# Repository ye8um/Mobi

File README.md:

# Mobi — Phone Controlled Two-Wheel Robot

Mobi is a compact, custom-designed Wi-Fi robot with an animated 0.96-inch OLED face. I designed its PCB in KiCad and its rounded enclosure, motor mounts, display opening, and power-bank compartment in Fusion 360. The robot uses a Seeed XIAO ESP32-C3, a TB6612FNG dual motor driver, and two small N20 gear motors. A small ball caster supports the body behind its drive wheels.

The goal is a simple, friendly robot that I can steer from my phone without installing an app. Mobi creates a Wi-Fi network and serves a web controller with directional buttons and a speed slider. The motor control stops when the button is released or commands stop arriving. Its OLED face blinks and shifts its eyes while turning.

## Features

- Phone control over a local Wi-Fi access point, no internet needed
- Forward, reverse, left, right, and stop
- Adjustable speed using PWM motor control
- Animated 128 × 64 OLED eyes
- 450 ms command timeout for a basic motor fail-safe
- Custom two-layer PCB and 3D-printed enclosure
- Two small N20 geared motors and a passive rear ball caster

There is **no obstacle or edge sensor** in this version, so operate it only on a level, clear floor, away from stairs, edges, and fragile objects. This is a hobby robot, not an autonomous robot.

## Hardware overview

Main controller: Seeed XIAO ESP32-C3 with its external Wi-Fi antenna. Motor controller: **bare** TB6612FNG SSOP-24 soldered to the custom PCB; not the breakout module. The TB6612's PWMA, PWMB, and STBY inputs are tied to 3.3 V in this board design. Display: common SSD1306 0.96-inch 128 × 64 **4-wire I2C** module, address usually 0x3C. Power: a commercial 5 V USB power bank, a **proper USB-C 5 V sink breakout**, an adequately rated power switch, and a Schottky diode feeding the XIAO VBUS input.

### Firmware pin map — updated after the pin swap

| XIAO label | GPIO | Function |
|---|---:|---|
| D1 | 3 | TB6612 AIN1 |
| D2 | 4 | TB6612 AIN2 |
| D3 | 5 | TB6612 BIN1 |
| D4 | 6 | TB6612 BIN2 (swapped) |
| D6 | 21 | OLED SDA (swapped) |
| D5 | 7 | OLED SCL |
| 3V3 | — | TB6612 VCC/PWMA/PWMB/STBY and compatible OLED VCC |
| GND | — | Common logic and motor ground |

Connect TB6612 AO1/AO2 to left motor and BO1/BO2 to right motor. Tie all TB6612 motor-supply VM and PGND pads correctly. The motor supply comes from the switched **5 V power input**, not from the XIAO 3.3 V output. The driver requires local decoupling as documented in its datasheet.

The XIAO's 5 V/VBUS supply must follow Seeed's external supply diode guidance. Do not connect the powered robot to your computer's USB port at the same time as its external 5 V source without reviewing the power arrangement.

## Arduino setup

1. Install Arduino IDE and Espressif's `esp32` board package.
2. Choose the **Seeed XIAO ESP32C3** board and its USB port.
3. From Arduino Library Manager install **Adafruit GFX Library** and **Adafruit SSD1306** (with their dependencies).
4. Open `Arduino/Mobi.ino`.
5. Check the pin assignments against the **latest actual KiCad schematic**, especially the changed D4/D6 pins.
6. Change `AP_PASSWORD` in the sketch. Upload the sketch with the robot's external power disconnected.
7. Test with the robot raised so the drive wheels cannot touch the floor. Start at low speed and verify both motor directions and the OLED.
8. Power the assembled robot, connect your phone to `Mobi-Robot`, then open `http://192.168.4.1`.
9. Press and hold a direction button to drive. Release to stop. The STOP button works immediately; a 450 ms timeout covers dropped commands.

If one motor turns backward, set `REVERSE_LEFT` or `REVERSE_RIGHT` to `true` in the sketch, then upload again. If the OLED remains blank, confirm its 3.3 V compatibility, 0x3C I2C address, SDA/SCL wires, and that it really uses an SSD1306 controller.

## CAD and assembly

The current concept has a 120 × 95 mm rounded chassis, a roughly 65 × 50 mm PCB, 2 mm outer walls, and a removable top cover. The display window is in the front. The battery-holder placeholder is 75 × 40 × 15 mm, **not a confirmed power-bank model**. Do not treat that placeholder as a purchase specification.

The motor CAD references are GA12-N20-sized, but must be compared against the purchased motor shaft and bracket dimensions. Wheel diameter changes the axle height, and the caster must touch the same floor plane as both wheels. For a 32 mm wheel and 8 mm chassis clearance, the axle center must be 8 mm above the chassis bottom. The earlier 24.5 mm shaft height assumed a 65 mm wheel, so it is **not compatible** with 32 mm wheels without adjusting the design.

Use the actual PCB STEP file for hole spacing, USB cutout location, and enclosure fit. Verify mounting screws, switch actuator clearance, PCB antenna keepout, and wire bends before printing the final body.

## Required files

- `Arduino/Mobi.ino`: complete phone-control firmware source (not hardware-tested)
- `BOM.csv` / `Mobi_BOM.xlsx`: all hardware, sourcing and validation notes
- `docs/Build_Checklist.md`: last checks before PCB order and assembly

KiCad and Fusion native source files are **not** in this package because the final versions were not provided for export; use your own saved project files.

## Current build status

The firmware is written, but it has **not been compiled on your machine or tested on actual Mobi hardware**. The selected main-power switch and USB-C input module require exact-part confirmation, and the power bank must be measured before the enclosure is finalized. The BOM separates confirmed product listings from estimates and placeholders. A custom PCB should not be ordered solely based on the firmware or generic links.

## Credits and references

- Seeed XIAO ESP32-C3 hardware guide: https://wiki.seeedstudio.com/XIAO_ESP32C3_Getting_Started/
- Toshiba TB6612FNG IC listing and datasheet: https://www.digikey.com/en/products/detail/toshiba-semiconductor-and-storage/TB6612FNG-C-8-EL/1730070
- Pololu 3/8-inch ball caster: https://www.pololu.com/product/951
- Pololu 32 mm wheel pair: https://www.pololu.com/product/1087
- ElectroPeak GA12-N20 motor/wheel kit listing: https://electropeak.com/n20-gear-motor-with-wheel

Mobi is my personal electronics and mechanical design project, with code and guidance developed for this build.

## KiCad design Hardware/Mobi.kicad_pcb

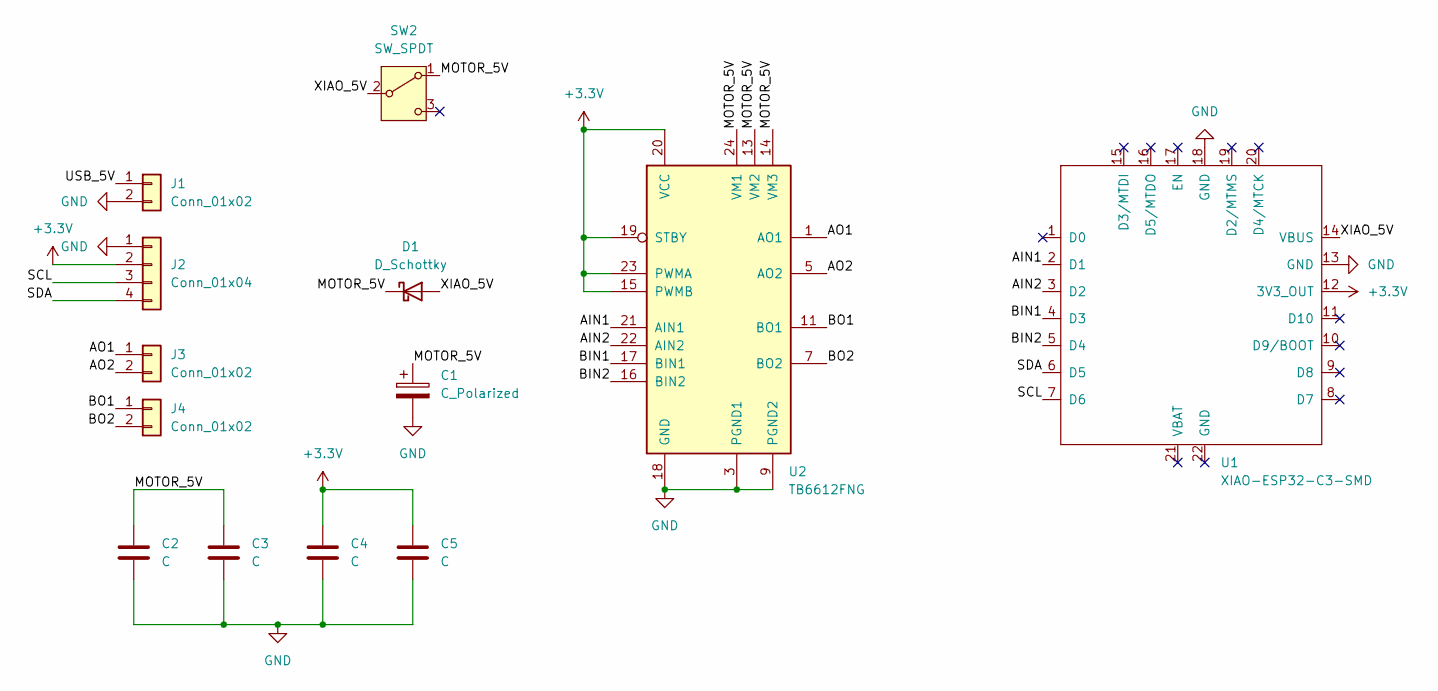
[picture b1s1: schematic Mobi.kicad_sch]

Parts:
C1: C_Polarized; CP_Radial_D8.0mm_P3.50mm
C2, C4: C; C_0805_2012Metric
C3, C5: C; C_1206_3216Metric
D1: D_Schottky; D_SMA
J1, J3, J4: Conn_01x02; PinHeader_1x02_P2.54mm_Vertical
J2: Conn_01x04; PinHeader_1x04_P2.54mm_Vertical
SW2: SW_SPDT; SW_SPDT_CK_JS102011SAQN
U1: XIAO-ESP32-C3-SMD; XIAO-ESP32-S3-SMD
U2: TB6612FNG; SSOP-24_5.3x8.2mm_P0.65mm

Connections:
+3.3V: C4.1, C5.1, J2.2, U1.12 (3V3_OUT), U2.15 (PWMB), U2.19 (STBY), U2.20 (VCC), U2.23 (PWMA)
/<NO NET>: C1.1, C2.1, C3.1, D1.1 (K), SW2.1 (A), U2.13 (VM2), U2.14 (VM3), U2.24 (VM1)
/AIN1: U1.2 (D1), U2.21 (AIN1)
/AIN2: U1.3 (D2), U2.22 (AIN2)
/AO1: J3.1, U2.1 (AO1), U2.2 (AO1)
/AO2: J3.2, U2.5 (AO2), U2.6 (AO2)
/BIN1: U1.4 (D3), U2.17 (BIN1)
/BIN2: U1.5 (D4), U2.16 (BIN2)
/BO1: J4.1, U2.11 (BO1), U2.12 (BO1)
/BO2: J4.2, U2.7 (BO2), U2.8 (BO2)
/SCL: J2.3, U1.7 (D6)
/SDA: J2.4, U1.6 (D5)
/USB_5V: J1.1
/XIAO_5V: D1.2 (A), SW2.2 (B), U1.14 (VBUS)
GND: C1.2, C2.2, C3.2, C4.2, C5.2, J1.2, J2.1, U1.13 (GND), U1.18 (GND), U2.3 (PGND1), U2.4 (PGND1), U2.9 (PGND2), U2.10 (PGND2), U2.18 (GND)

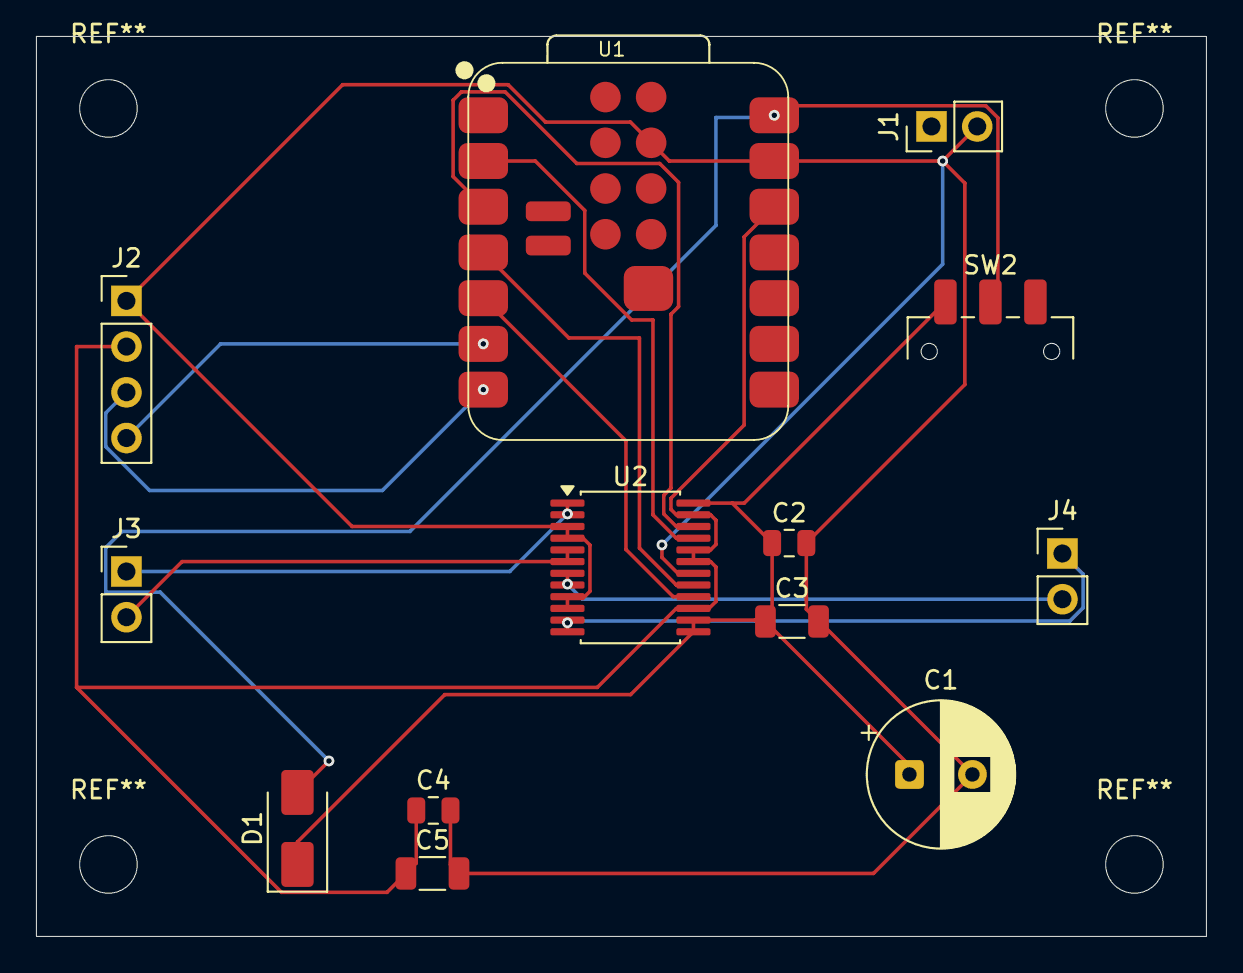
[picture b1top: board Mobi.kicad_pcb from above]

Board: 2 copper layers, 65.0 x 50.0 mm, 13 parts (0 on the bottom side), 14 nets.

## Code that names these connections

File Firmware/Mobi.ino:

/*
  MOBI v1 — Wi-Fi phone-controlled two-wheel robot
  Target: Seeed XIAO ESP32-C3, bare TB6612FNG, SSD1306 128x64 I2C OLED.
  Uses the REVISED pin swap discussed in the build:
  D4/GPIO6 = BIN2, D6/GPIO21 = OLED SDA, D5/GPIO7 = OLED SCL.
  TB6612 PWMA, PWMB, STBY must be tied to 3.3 V in hardware.
  5V motor supply and common ground required. Never power motors from 3V3.
  Requires Adafruit GFX + Adafruit SSD1306 libraries and esp32 board package.
  Not tested with the physical Mobi PCB; verify wiring and directions first.
*/
#include <Arduino.h>
#include <WiFi.h>
#include <WebServer.h>
#include <Wire.h>
#include <Adafruit_GFX.h>
#include <Adafruit_SSD1306.h>

constexpr uint8_t AIN1_PIN = 3;   // XIAO D1
constexpr uint8_t AIN2_PIN = 4;   // XIAO D2
constexpr uint8_t BIN1_PIN = 5;   // XIAO D3
constexpr uint8_t BIN2_PIN = 6;   // XIAO D4 (swapped)
constexpr uint8_t OLED_SDA_PIN = 21; // XIAO D6 (swapped)
constexpr uint8_t OLED_SCL_PIN = 7;  // XIAO D5
constexpr uint8_t OLED_ADDR = 0x3C;

// Reverse either motor in software if its wheel runs backward.
constexpr bool REVERSE_LEFT = false;
constexpr bool REVERSE_RIGHT = false;
// Stop when no command has been renewed for this many milliseconds.
constexpr uint32_t DEADMAN_MS = 450;
constexpr uint32_t FRAME_MS = 70;
constexpr uint8_t DEFAULT_SPEED = 55;
constexpr uint8_t MAX_DUTY = 220; // cap speed for initial testing

const char* AP_NAME = "Mobi-Robot";
const char* AP_PASSWORD = "mobi2026drive"; // change before using in public

WebServer server(80);
Adafruit_SSD1306 oled(128, 64, &Wire, -1);
bool oledOK = false;
uint8_t speedPercent = DEFAULT_SPEED;
uint32_t lastCommandMs = 0;
uint32_t lastFrameMs = 0;
uint32_t lastBlinkMs = 0;
uint32_t blinkAtMs = 0;
char movement = 'S';
bool blinking = false;

const char PAGE[] PROGMEM = R"HTML(
<!DOCTYPE html><html lang="en"><head><meta charset="utf-8">
<meta name="viewport" content="width=device-width,initial-scale=1,user-scalable=no">
<title>Mobi Controller</title><style>
:root{font-family:system-ui,sans-serif;color:#17263b;background:#f4f8fc}
body{max-width:430px;margin:0 auto;padding:24px 18px;text-align:center}
h1{margin:6px 0 0;font-size:2rem}p{color:#617083}
.panel{background:white;border:1px solid #dae3ed;border-radius:22px;padding:22px;box-shadow:0 10px 35px #142c4814}
#status{padding:12px;border-radius:12px;background:#eaf3ff;font-weight:700;letter-spacing:.08em}
.pad{display:grid;grid-template-columns:repeat(3,1fr);gap:12px;margin-top:20px}
button{border:0;border-radius:18px;background:#1663b4;color:white;font-size:30px;height:75px;touch-action:none;user-select:none;-webkit-user-select:none}
button:active,.held{background:#0d396f;transform:scale(.97)}
.stop{background:#d14a4a}.blank{visibility:hidden}
label{display:flex;justify-content:space-between;margin:20px 0 10px}input{width:100%}
.small{font-size:13px;margin-top:20px}
</style></head><body><h1>◉ MOBI</h1><p>Wi-Fi robot controller</p>
<div class="panel"><div id="status">STOPPED</div>
<div class="pad"><div class="blank"></div><button data-dir="F">↑</button><div class="blank"></div>
<button data-dir="L">←</button><button class="stop" id="stop">■</button><button data-dir="R">→</button>
<div class="blank"></div><button data-dir="B">↓</button><div class="blank"></div></div>
<label for="speed">Speed <strong><span id="speedText">55</span>%</strong></label>
<input type="range" id="speed" min="0" max="100" value="55" step="5">
<p class="small">Hold a direction to move. Release to stop.<br>Use only on a clear, flat floor; there is no edge sensor.</p></div>
<script>
let held='S', timer=null;
const label=document.getElementById('status'),speed=document.getElementById('speed');
const names={F:'FORWARD',B:'REVERSE',L:'LEFT',R:'RIGHT',S:'STOPPED'};
function transmit(dir){fetch('/cmd?dir='+dir+'&speed='+speed.value,{cache:'no-store'}).catch(()=>{});}
function stop(){held='S';clearInterval(timer);timer=null;label.textContent='STOPPED';transmit('S');document.querySelectorAll('button').forEach(b=>b.classList.remove('held'));}
function start(dir,button){stop();held=dir;label.textContent=names[dir];button.classList.add('held');transmit(dir);timer=setInterval(()=>transmit(held),160);}
document.querySelectorAll('button[data-dir]').forEach(button=>{
 button.addEventListener('pointerdown',e=>{e.preventDefault();button.setPointerCapture(e.pointerId);start(button.dataset.dir,button);});
 button.addEventListener('pointerup',e=>{e.preventDefault();stop();});
 button.addEventListener('pointercancel',stop);
 button.addEventListener('lostpointercapture',stop);
});
document.getElementById('stop').addEventListener('click',stop);
speed.addEventListener('input',()=>{document.getElementById('speedText').textContent=speed.value;if(held!=='S')transmit(held);});
window.addEventListener('blur',stop);document.addEventListener('visibilitychange',()=>{if(document.hidden)stop();});
window.addEventListener('pagehide',stop);
</script></body></html>
)HTML";

void setOneMotor(uint8_t pin1, uint8_t pin2, int requested, bool invert) {
  if (invert) requested = -requested;
  requested = constrain(requested, -255, 255);
  if (requested > 0) {
    analogWrite(pin1, requested); analogWrite(pin2, 0);
  } else if (requested < 0) {
    analogWrite(pin1, 0); analogWrite(pin2, -requested);
  } else {
    analogWrite(pin1, 0); analogWrite(pin2, 0);
  }
}

void drive(char dir, uint8_t percent) {
  const int duty = map(constrain(percent, 0, 100), 0, 100, 0, MAX_DUTY);
  int l = 0, r = 0;
  switch (dir) {
    case 'F': l = duty; r = duty; break;
    case 'B': l = -duty; r = -duty; break;
    case 'L': l = -duty; r = duty; break;
    case 'R': l = duty; r = -duty; break;
    default: dir = 'S'; break;
  }
  setOneMotor(AIN1_PIN, AIN2_PIN, l, REVERSE_LEFT);
  setOneMotor(BIN1_PIN, BIN2_PIN, r, REVERSE_RIGHT);
  movement = dir;
}

void handleCmd() {
  if (!server.hasArg("dir")) { server.send(400,"text/plain","Missing dir"); return; }
  String arg = server.arg("dir");
  if (arg.length()!=1 || String("FBLRS").indexOf(arg.charAt(0))<0) {
    server.send(400,"text/plain","Bad direction"); return;
  }
  const char dir = arg.charAt(0);
  if (server.hasArg("speed")) speedPercent = constrain(server.arg("speed").toInt(),0,100);
  lastCommandMs = millis();
  drive(dir,speedPercent);
  server.sendHeader("Cache-Control","no-store");
  server.send(200,"text/plain","OK");
}

void drawEyes() {
  if (!oledOK) return;
  oled.clearDisplay();
  const bool moving = movement != 'S';
  if (blinking) {
    oled.drawFastHLine(24, 32, 28, SSD1306_WHITE);
    oled.drawFastHLine(76, 32, 28, SSD1306_WHITE);
  } else {
    oled.fillRoundRect(23, 15, 28, 36, 11, SSD1306_WHITE);
    oled.fillRoundRect(77, 15, 28, 36, 11, SSD1306_WHITE);
    int offset = movement == 'L' ? -5 : movement == 'R' ? 5 : 0;
    oled.fillCircle(36+offset,33,5,SSD1306_BLACK);
    oled.fillCircle(90+offset,33,5,SSD1306_BLACK);
  }
  if (moving) oled.drawPixel(63, 56, SSD1306_WHITE);
  oled.display();
}

void setup() {
  Serial.begin(115200);
  pinMode(AIN1_PIN,OUTPUT); pinMode(AIN2_PIN,OUTPUT);
  pinMode(BIN1_PIN,OUTPUT); pinMode(BIN2_PIN,OUTPUT);
  drive('S',0);
  Wire.begin(OLED_SDA_PIN,OLED_SCL_PIN);
  oledOK = oled.begin(SSD1306_SWITCHCAPVCC,OLED_ADDR);
  if (!oledOK) Serial.println("OLED not found; verify 0x3C and swapped SDA/SCL wiring");
  else {oled.clearDisplay(); oled.setTextSize(1); oled.setTextColor(SSD1306_WHITE); oled.setCursor(25,26); oled.print("MOBI STARTING"); oled.display();}
  WiFi.mode(WIFI_AP);
  bool apOK = WiFi.softAP(AP_NAME,AP_PASSWORD);
  Serial.printf("AP started: %s | IP: %s\n",apOK?"YES":"NO",WiFi.softAPIP().toString().c_str());
  server.on("/",HTTP_GET,[]{server.send_P(200,"text/html",PAGE);});
  server.on("/cmd",HTTP_GET,handleCmd);
  server.onNotFound([]{server.send(404,"text/plain","Not found");});
  server.begin();
  lastCommandMs = millis(); blinkAtMs = millis()+2900;
}

void loop() {
  server.handleClient();
  const uint32_t now = millis();
  if (movement != 'S' && now-lastCommandMs > DEADMAN_MS) drive('S',0);
  if (!blinking && (int32_t)(now-blinkAtMs)>=0) {blinking=true; lastBlinkMs=now;}
  if (blinking && now-lastBlinkMs>=140) {blinking=false; blinkAtMs=now+3000+(now%2500);}
  if (now-lastFrameMs>=FRAME_MS) {lastFrameMs=now; drawEyes();}
}
